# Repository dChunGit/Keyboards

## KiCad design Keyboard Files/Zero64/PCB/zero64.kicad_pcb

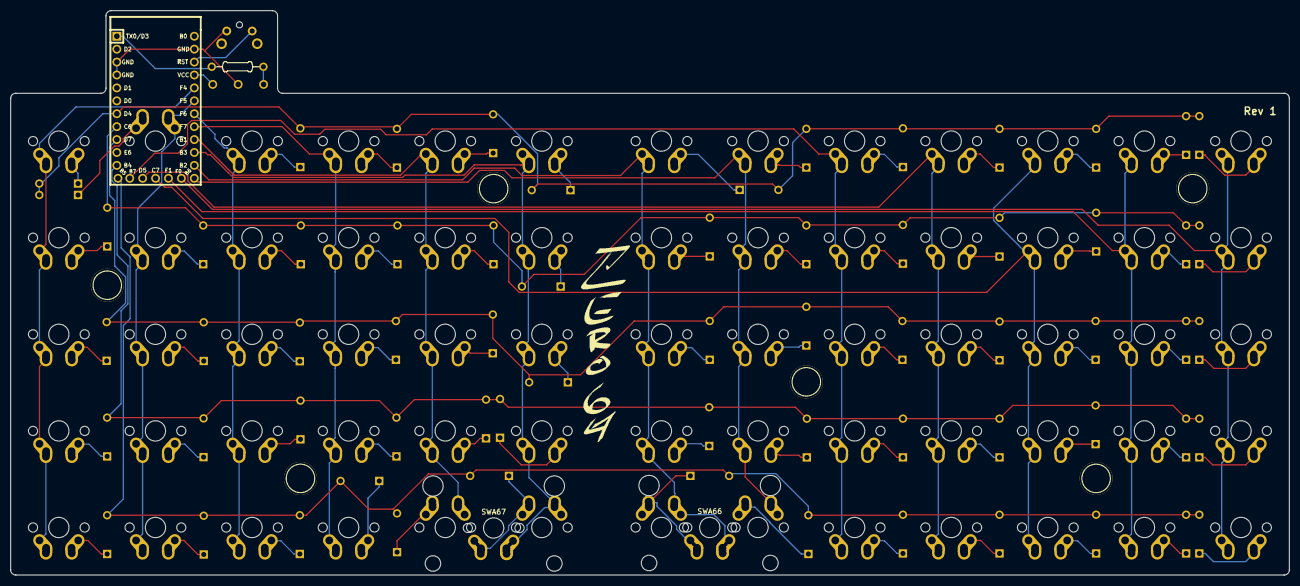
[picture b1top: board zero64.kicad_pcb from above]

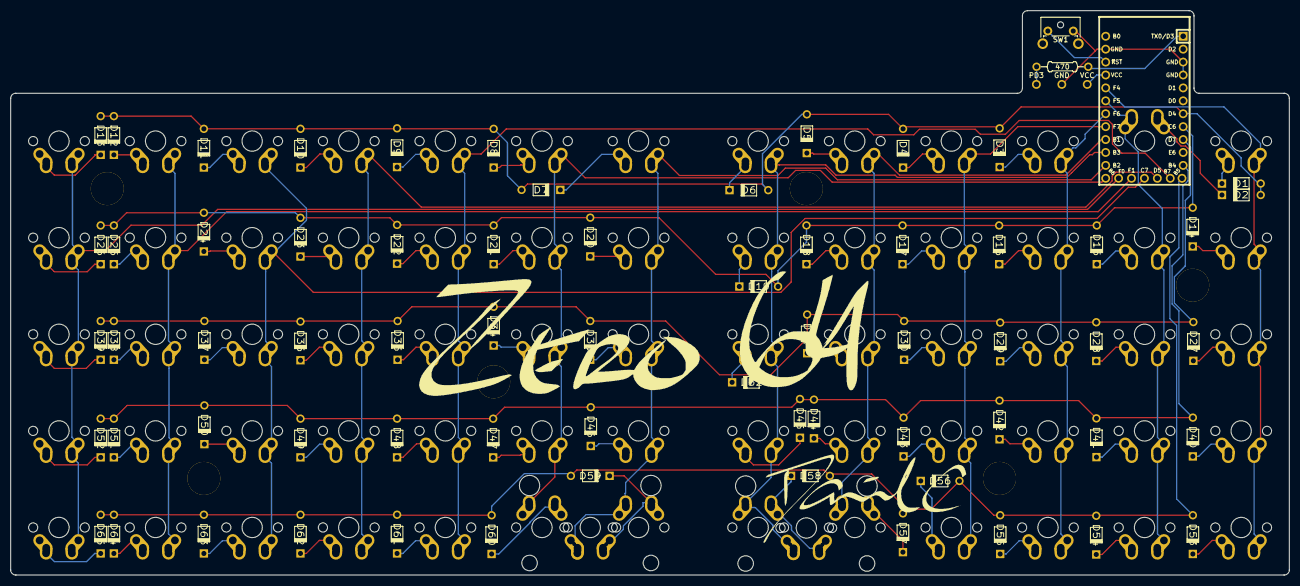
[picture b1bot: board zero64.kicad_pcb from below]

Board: 2 copper layers, 251.5 x 111.0 mm, 147 parts (72 on the bottom side), 88 nets.

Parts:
D1, D2, D3, D4, D5, D6, D7, D8, D9, D10, D11, D12, D13, D14, D15, D16, D17, D18, D19, D20, D21, D22, D23, D24, D25, D26, D27, D28, D29, D30, D31, D32, D33, D34, D35, D36, D37, D38, D39, D40, D41, D42, D43, D44, D45, D46, D47, D48, D49, D50, D51, D52, D53, D54, D55, D56, D57, D58, D59, D60, D61, D62, D63, D64, D65: D; Diode
H1, H2, H3, H4, H5, H6: Hole; MountingHole
Horiz: LOGO; zero64_large
R1: 470; Resistor
SW1: SW_PUSH; SW_Tactile_SPST_Angled_MJTP1117
SWA1, SWA2, SWA3, SWA4, SWA5, SWA6, SWA7, SWA8, SWA9, SWA10, SWA11, SWA12, SWA13, SWA14, SWA15, SWA16, SWA17, SWA18, SWA19, SWA20, SWA21, SWA22, SWA23, SWA24, SWA25, SWA26, SWA27, SWA28, SWA29, SWA30, SWA31, SWA32, SWA33, SWA34, SWA35, SWA36, SWA37, SWA38, SWA39, SWA40, SWA41, SWA42, SWA43, SWA44, SWA45, SWA46, SWA47, SWA48, SWA49, SWA50, SWA51, SWA52, SWA53, SWA54, SWA55, SWA56, SWA57, SWA58, SWA59, SWA60, SWA61, SWA62, SWA63, SWA64, SWA65: SW_PUSH; Hybrid_PCB_100H_Dual_hole-nosilk-flip
SWA66, SWA67: SW_PUSH; Hybrid_PCB_200H-dual-nosilk
Sig: LOGO; signature_part
TP1: PD3; SinglePad
TP2: VCC; SinglePad
TP3: GND; SinglePad
U1: Elite-C
Vert: LOGO; zero64_vert_small

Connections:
Col0: SWA1.1, SWA14.1, SWA27.1, SWA40.1, SWA53.1, U1.20
Col1: SWA2.1, SWA15.1, SWA28.1, SWA41.1, SWA54.1, U1.19
Col2: SWA3.1, SWA16.1, SWA29.1, SWA42.1, SWA55.1, U1.18
Col3: SWA4.1, SWA17.1, SWA30.1, SWA43.1, SWA56.1, U1.17
Col4: SWA5.1, SWA18.1, SWA31.1, SWA44.1, SWA57.1, U1.16
Col5: SWA6.1, SWA19.1, SWA32.1, SWA45.1, SWA58.1, SWA67.1, U1.15
Col6: SWA7.1, SWA20.1, SWA33.1, SWA46.1, SWA59.1, SWA66.1, U1.14
Col7: SWA8.1, SWA21.1, SWA34.1, SWA47.1, SWA60.1, U1.13
Col8: SWA9.1, SWA22.1, SWA35.1, SWA48.1, SWA61.1, U1.25
Col9: SWA10.1, SWA23.1, SWA36.1, SWA49.1, SWA62.1, U1.26
Col10: SWA11.1, SWA24.1, SWA37.1, SWA50.1, SWA63.1, U1.27
Col11: SWA12.1, SWA25.1, SWA38.1, SWA51.1, SWA64.1, U1.28
Col12: SWA13.1, SWA26.1, SWA39.1, SWA52.1, SWA65.1, U1.29
GND: SW1.2, TP3.1, U1.3, U1.4, U1.23
unnamed: D1.2, SWA1.2
unnamed: D2.2, SWA2.2
unnamed: D3.2, SWA3.2
unnamed: D4.2, SWA4.2
unnamed: D5.2, SWA5.2
unnamed: D6.2, SWA6.2
unnamed: D7.2, SWA7.2
unnamed: D8.2, SWA8.2
unnamed: D9.2, SWA9.2
unnamed: D10.2, SWA10.2
unnamed: D11.2, SWA11.2
unnamed: D12.2, SWA12.2
unnamed: D13.2, SWA13.2
unnamed: D14.2, SWA14.2
unnamed: D15.2, SWA15.2
unnamed: D16.2, SWA16.2
unnamed: D17.2, SWA17.2
unnamed: D18.2, SWA18.2
unnamed: D19.2, SWA19.2
unnamed: D20.2, SWA20.2
unnamed: D21.2, SWA21.2
unnamed: D22.2, SWA22.2
unnamed: D23.2, SWA23.2
unnamed: D24.2, SWA24.2
unnamed: D25.2, SWA25.2
unnamed: D26.2, SWA26.2
unnamed: D27.2, SWA27.2
unnamed: D28.2, SWA28.2
unnamed: D29.2, SWA29.2
unnamed: D30.2, SWA30.2
unnamed: D31.2, SWA31.2
unnamed: D32.2, SWA32.2
unnamed: D33.2, SWA33.2
unnamed: D34.2, SWA34.2
unnamed: D35.2, SWA35.2
unnamed: D36.2, SWA36.2
unnamed: D37.2, SWA37.2
unnamed: D38.2, SWA38.2
unnamed: D39.2, SWA39.2
unnamed: D40.2, SWA40.2
unnamed: D41.2, SWA41.2
unnamed: D42.2, SWA42.2
unnamed: D43.2, SWA43.2
unnamed: D44.2, SWA44.2
unnamed: D45.2, SWA45.2
unnamed: D46.2, SWA46.2
unnamed: D47.2, SWA47.2
unnamed: D48.2, SWA48.2
unnamed: D49.2, SWA49.2
unnamed: D50.2, SWA50.2
unnamed: D51.2, SWA51.2
unnamed: D52.2, SWA52.2
unnamed: D53.2, SWA53.2
unnamed: D54.2, SWA54.2
unnamed: D55.2, SWA55.2
unnamed: D56.2, SWA56.2
unnamed: D57.2, SWA57.2
unnamed: D58.2, SWA58.2, SWA67.2
unnamed: D59.2, SWA59.2, SWA66.2
unnamed: D60.2, SWA60.2
unnamed: D61.2, SWA61.2
unnamed: D62.2, SWA62.2
unnamed: D63.2, SWA63.2
unnamed: D64.2, SWA64.2
unnamed: D65.2, SWA65.2
unnamed: R1.1, U1.1
unnamed: R1.2, TP1.1
unnamed: SW1.1, U1.22
Row0: D1.1, D2.1, D3.1, D4.1, D5.1, D6.1, D7.1, D8.1, D9.1, D10.1, D11.1, D12.1, D13.1, U1.7
Row1: D14.1, D15.1, D16.1, D17.1, D18.1, D19.1, D20.1, D21.1, D22.1, D23.1, D24.1, D25.1, D26.1, U1.8
Row2: D27.1, D28.1, D29.1, D30.1, D31.1, D32.1, D33.1, D34.1, D35.1, D36.1, D37.1, D38.1, D39.1, U1.9
Row3: D40.1, D41.1, D42.1, D43.1, D44.1, D45.1, D46.1, D47.1, D48.1, D49.1, D50.1, D51.1, D52.1, U1.11
Row4: D53.1, D54.1, D55.1, D56.1, D57.1, D58.1, D59.1, D60.1, D61.1, D62.1, D63.1, D64.1, D65.1, U1.12
VCC: TP2.1, U1.21
